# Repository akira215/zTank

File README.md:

# zTank
Tank survey, embedded sofware on dedicated PCB using ESP32C6 µC

# Description

This repository contain all the development for an electronic device that will monitor a water tank (such as rain collect tank) using zigbee to transmit data to a coordinator. It contains: 
 * A PCB design [PCB design](PCB/README.md)
 * An enclosure design to be printed in 3D [Enclosure design](3Dprint/README.md)
 * Source code of the embedded software on the board (in an ESP32C6 µC)
 * An External converter for Zigbee2MQTT service [external converter](external_converters)

# Principle

The board will collect data from various sensors surch as:
 * Upstream static pressure (pump side)
 * Downstream static pressure (home side) - difference between upstream and downstream static pressure is used to estimate filters clogging
 * Water level sensor, to estimate the available water volume in the tank
 * water pulse meter to count the consumption in the home
 * Additionally on board temperature sensor could be monitor

 The 3 first sensors shall be 4-20mA sensor directly connected to the board. The water counter shall be a dry contact meter, connected to the board

 All these sensors have a calibration factor that can be updated directly form Zigbee2MQTT GUI. To avoid losing calibration, the device itself will keep updated theses factor in its Non Volatile Storage.

A 4-20mA input is available for any other futher sensor requirement. Adding a sensor will require to :
 * Update the embedded software
 * Update the external converter on Zigbee2MQTT side

## Usage

  * Short press button to join the zigbee network (coordinator shall grant pairing) -> LED shall flash, until network is joined, it then shutoff
  * Long press button to leave network. When the LED is fixed on, the device is not connected to the network neither is trying to join

## Sensor selection

### Upstream and downstream static pressure

  Regular pressure transmitter are not so expensive and efficient for that purpose. These 2 sensors shall have a measured range according to installation pressure. In regular network, pressure is limited to 3 bars, so selecting a sensor 0-5 bars seems a good choice. If the upper value is higher, the resolution of the measurement will be less as the ADC converter resolution is fixed.

  The shunt to convert current to tension for the ADC converter is 133R, and Imax for the sensor @max range will be 20mA so Umax for ADS1115 will be 2.66V (U=R*I). 5 bars = 500 kPa, so the calibration factor shall be 500 kPa / 2.66V = 187.97 kPa/V. Of course this factor shall be adjusted by measuring at the same location of one sensor the pressure, and correcting the reading of the sensor, but this short computation can help to start setting up calibration factor

### Water level

  Whatever technology of sensor could be used as soon as its output is 4-20mA current. Tests have been done using submerged differential pressure sensor, with the balance pipe to get the atmospheric pressure that run with the electrical cable, they worked properly. The range of this sensor shall be in accordance with the depth of the tank. The output value of Zigbee2MQTT will be a % of depth (meaning 100% when tank is full). Depending on the shape and cross section of the tank, this could be converted to a volume directly in the Z2M external converter, or outside Z2M in another software.

  The shunt to convert current to tension for the ADC converter is 133R, and Imax for the sensor @max range will be 20mA so Umax for ADS1115 will be 2.66V (U=R*I). For 100% the calibration factor shall be 100% / 2.66V = 37.594 %/V. 
  
  Of course this factor shall be adjusted when tank is full to read 100% in the Zigbee2MQTT output. For example, if yo have a 0-2m sensor and the require stroke of your tank (max height - min height before depriming pump) is 1.5m, it means that the 100% value of your tank will occur when sensor will read 1.5m (take care to install the sensor just before depriming pump). The voltage at the converter will be 1.5m/2m * 2.66V = 1.995V, so you will have to set the calibration factor considering 100% / 1.995V = 50.125%/V

### Water pulse counter

  The water meter shall send a pulse each XX L, whatever XX is. It is expected to have a dry contact that switch on and off each pulse. Hardware debouncer has been implemented for a particular counter, measuring bouncing using an oscilloscope. Computation of this RC filter has been provided here:
  [Spreadsheet](<PCB/2024-06-29 Comput.ods>)
    
  The kFactor to be set up in Zigbee2MQTT is only the L per pulse of the counter.

## Zigbee2MQTT integration

### External converter

External converter shall be loaded according to Zigbee2MQTT instructions:

[Zigbee2MQTT external converters](https://www.zigbee2mqtt.io/advanced/more/external_converters.html)

Restart Zigbee2MQTT `Webpage > Settings > Tools > Restart Zigbee2MQTT`

### Pairing zTank device

If the LED is fixed on, short press one time on the button, this will put the device in pairing mode.
Device is in Pairing Mode when the LED flahes quickly. 

Put Coordinator (or other device) in pairing mode using Zigbee2MQTT GUI (antenna symbol on the upper right of the screen with mention `All`)

After a short time, LED shall stop flashing. When LED is off, device is paired. You can check on Zigbee2MQTT device list

### Device icon

To add an icon in Zigbee2MQTT GUI, create a folder named `device_icon` in the root of Zigbee2MQTT docker installation (folder containing `configuration.yml`). In that foler, put the `zTank_icon.png` file contained in the `img` directory of this repository.

On Zigbee2MQTT GUI, go to `Devices` list and click on the device. Go to `Settings` tab and scroll down to the `icon` box.
Put `device_icons/zTank_icon.png` in that box. Icon shall be visible on Zigbee2MQTT GUI.

### Reporting

To develop*******************************************************************

## Build Instructions

The embedded software required `esp-ash-components`:

```
git submodule add https://github.com/akira215/esp-ash-components.git components
```

Create a partition.csv for zigbee and configure menuconfig with custom partition table (shall be done by default)

## Configuration

Configuration is available in `menuconfig` in the `Project setting` section:

### Pin Layout

  This section refer to hardware connection of LED button and volume meter. <span style="color:red">**These settings shall not be changed unless new hardware is developped.**</span>

### Zigbee endpoints

  This section refer to the endpoint for each sensor of the device. Any change in this number require to update the external converter accordingly

  And in Zigbee2MQTT external converter:

### Zigbee device

  Zigbee stack has been sized doing extensive tests. <span style="color:red">**This setting shall not be changed.**</span>

### ADS Pin Layout

  This section refer to hardware connection of ADS1115 converter to µC pin. <span style="color:red">**These settings shall not be changed unless new hardware is developped.**</span>

### ADS Converter config

  The first 3 inputs refer to the channel in which each sensor is connected. Take care that channel are not implemented on the connector in a logical order, so please refer to pictures that describe which pins of the connector is connected to which ADC channel (and polarity for sensors)

  The delay between 2 queries of ADS is the update rate of the measurement. Between 2 measurement, ADS is put in sleep to optimize consumption. Take care that driver will trigger one conversion for each channel, so there is a minimal time between 2 queries, depending on the resolution set for the ADS.

  The delay between 2 queries of temperature is the update rate of the measurement of the internal µC temperature sensor.

## Current Status

Still work in progress, but is completely running. All bugs 
could be reported to try to improve it.

## PCB design

[PCB design](PCB/README.md)

## Enclosure design design

[Enclosure design](3Dprint/README.md)

## Caveats

### To be developped

OTA update

## Usage and Examples

## Changes

### New in version 0.0.0

## Credits

 * [Zigbee2MQTT](https://github.com/Koenkk/zigbee2mqtt)

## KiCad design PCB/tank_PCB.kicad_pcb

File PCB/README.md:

# zTank PCB
A dedicated PCB using ESP32C6 µC as been designed to optimize reliability and costs.

## Tools

 The design of the PCB has been done with KiCad 9.0. Particular footprint and 3D STEP file are included in the `/footprints` folder for sake of maintenance

## Design

 The design is based on ESP32C6 WROOM with the following peripherials:
 - USB for power, flash device and output serial debug / info.
 - Powering circuit is done using MCP1826S 
 - A 4-20mA loop is built based on a LM2735X (1.6MHz) to raise voltage to about 20V
 - 4 channels 4-20mA sensors is provided and converted using ADS1115IDGS. It communicate with µC with i2c port
 - a debounced contact is provided for pulse counter
 - A push button is also provided for very simple HMI
 - PCB is also equipped by a LED for simpl HMI
 - Finally PCB is equipped with header that can be used for a touchscreen device in case of future needs (software lib already written and tested)

 Component size has been selected to 0805, except ESD protective diodes that are smaller.

### USB

  USB socket is grounded to the main ground planes (2 sides).
  USB Lines `USB-` and `USB+` are directly connected to ESP32C6 to flash and monitor µC.
  `VBUS` is used to provide `+5V` (which is in fact lower than +5V) via a protective diode `D3`.

  All this 3 lines are protected by ESD protective diode.

### Voltage regulator

  All the board is powered using `+3.3V`. This voltage is provided by a fixed low-voltage regulator MCP1826S-3302E that can provide up to 1000mA.
  Fixed voltage regulator requires only few external component, in this case only capacitors are installed as per datasheet.

### 4-20mA Voltage circuit

  To avoid noise on lines and due to voltage drop at each stage, 4-20mA loop voltage shall be at around 20V. Care shall be taken when changing this voltage as it may require adjustment (in the shunt values for instance) to avoid damaging other components.

  This voltage is produced from `+5V` using a boost type regulator LM2735X (@1.6MHz). Computation of the external components are provided in the LibreOffice Spreadsheet [PCB comput spreadsheet](<2024-06-29 Comput.ods>). A 33µH inductance has been selected to get a clean output voltage to avoid noise on sensors line.

### 4-20mA conversion

  4 channels are available via Phoenix contact 8 poles connector. Each channel input current is injected in a 133R shunt (low tolerance resistor) to output a voltage below 3.3V. A 100nF capacitor is provided to reduce noise.

  Each channel voltage is then converted in a digital signal using an ADS1115IDGS, that communicate with µC using i2c protocol. A ready pin is used to trigger an interrupt to the µC when data are available.
  External components are:
   - 10k resistor connected to the ground for the address of the device (only one on board so gnd is the common one)
   - 10k pull-up resistor on each signal (`SCL`, `SDA`, `RDY`) connected to µC
   - decoupling capacitor for power lines and rearmable fuse to protect circuit

### Debounced contact

### µC ESP32C6 WROOM

### Push Button

### Led

### Header

## PCB fabrication

## Assembly

## Usage

### To be developped

## Credits

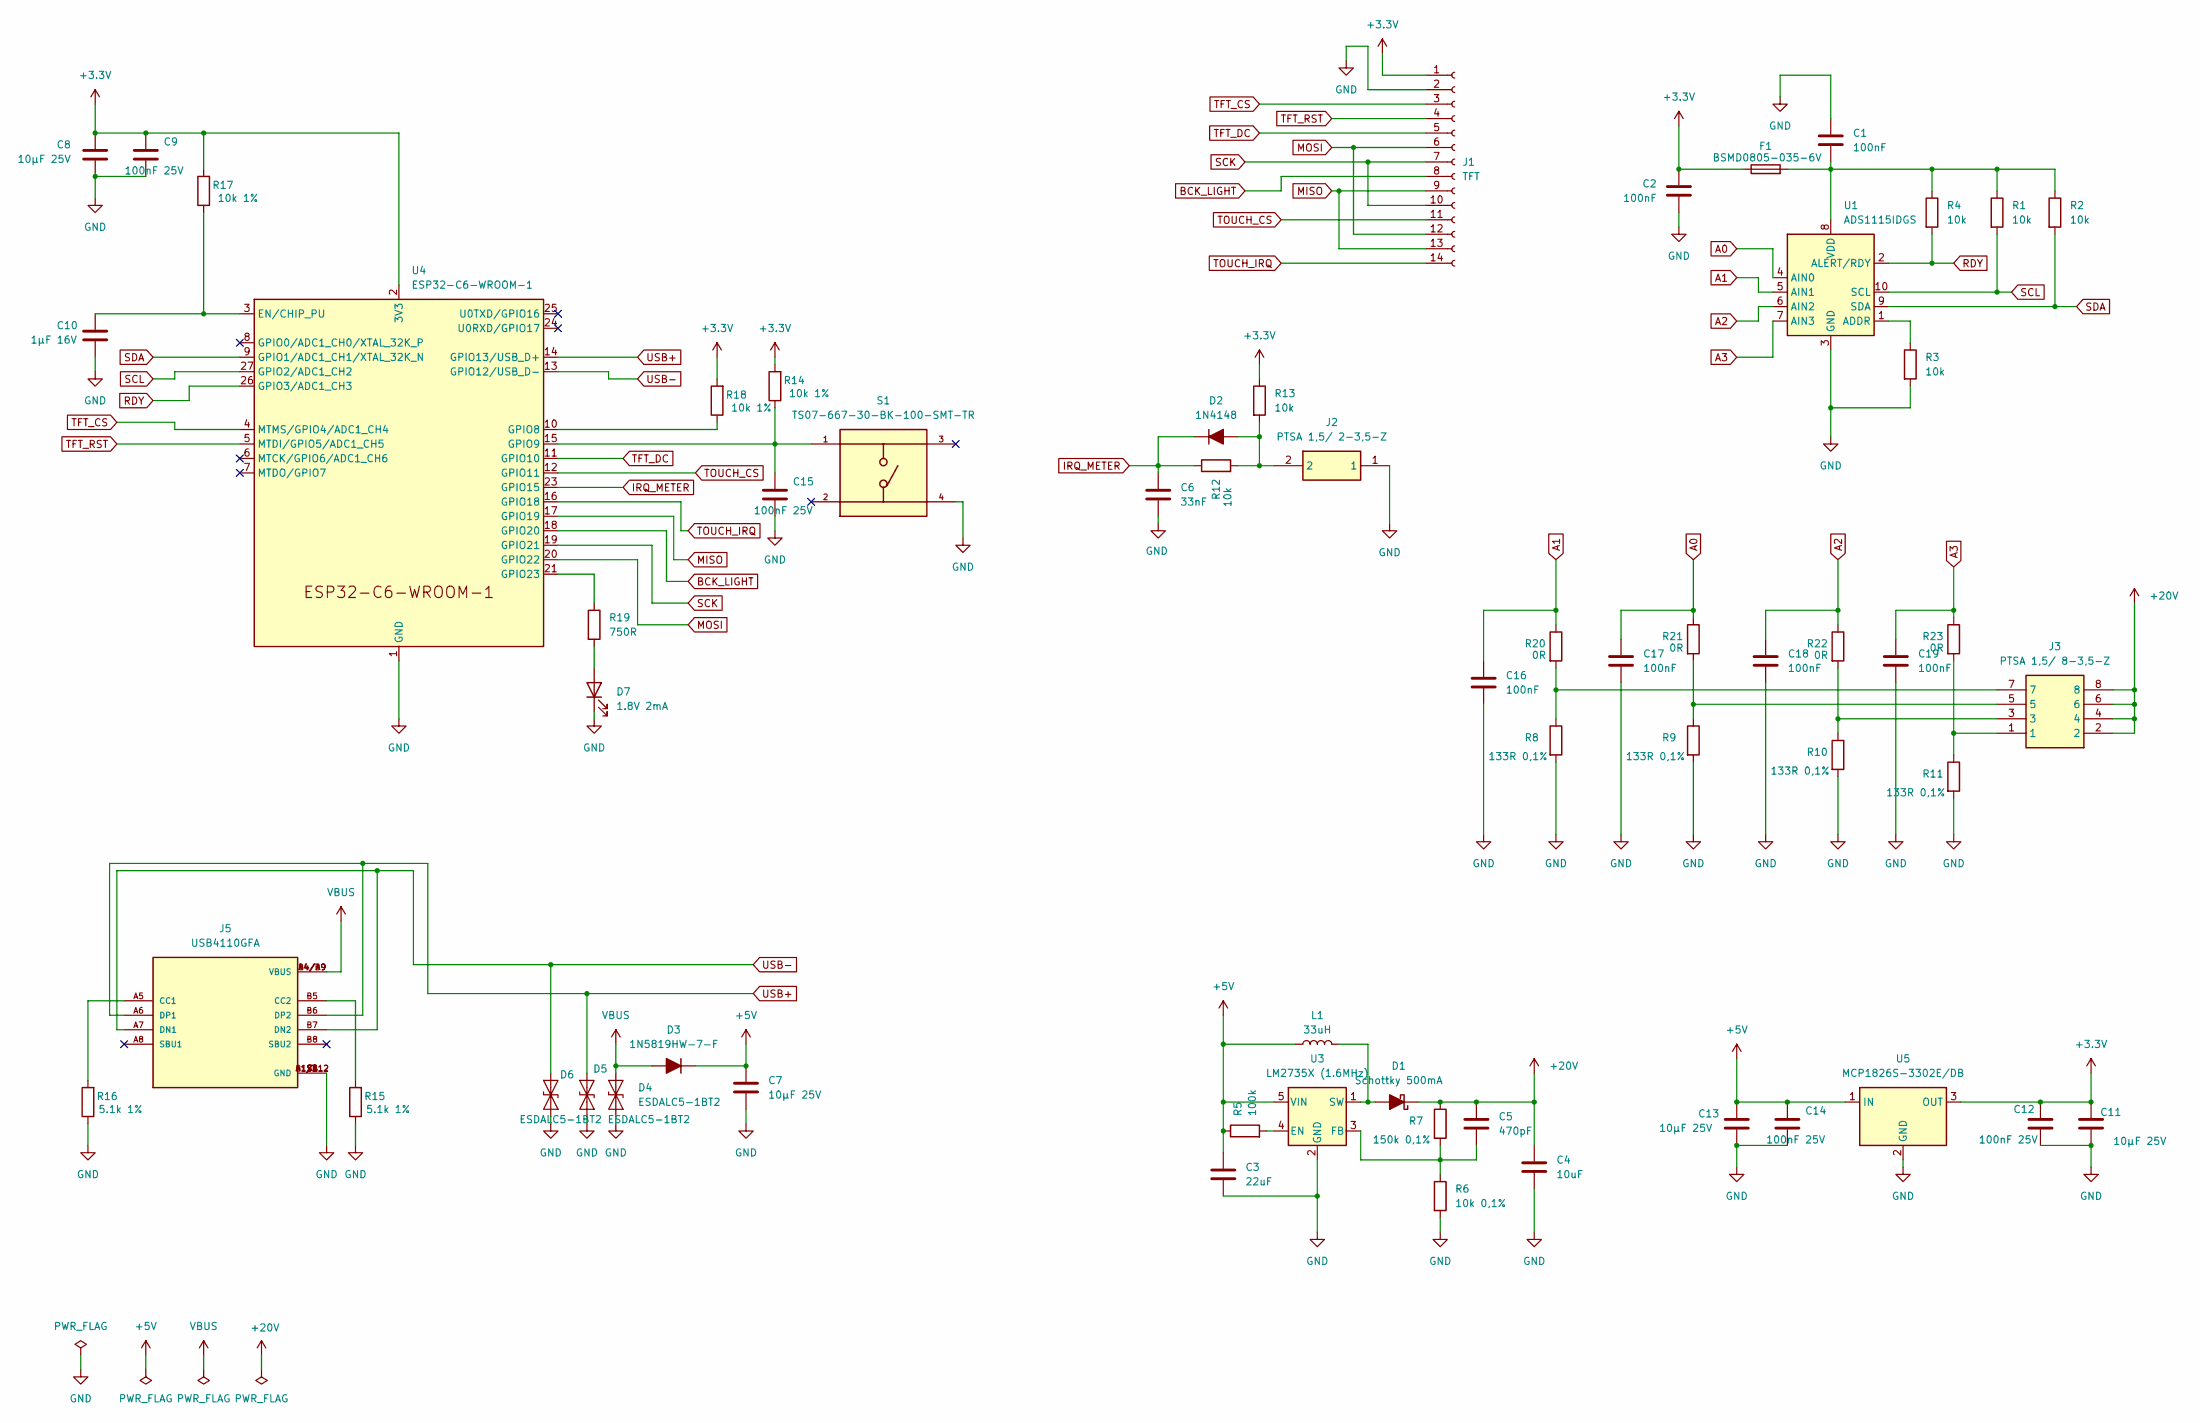
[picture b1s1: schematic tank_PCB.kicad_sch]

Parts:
C1, C2, C16, C17, C18, C19: 100nF; C_0805_2012Metric_Pad1.18x1.45mm_HandSolder
C3: 22uF; C_0805_2012Metric_Pad1.18x1.45mm_HandSolder
C4: 10uF; C_0805_2012Metric_Pad1.18x1.45mm_HandSolder
C5: 470pF; C_0805_2012Metric_Pad1.18x1.45mm_HandSolder
C6: 33nF; C_0805_2012Metric_Pad1.18x1.45mm_HandSolder
C7, C8, C11, C13: 10µF 25V; C_0805_2012Metric_Pad1.18x1.45mm_HandSolder
C9, C12, C14, C15: 100nF 25V; C_0805_2012Metric_Pad1.18x1.45mm_HandSolder
C10: 1µF 16V; C_0805_2012Metric_Pad1.18x1.45mm_HandSolder
D1: Schottky 500mA; D_SOD-123
D2: 1N4148; D_SOD-323_HandSoldering
D3: 1N5819HW-7-F; D_SOD-123
D4, D5, D6: ESDALC5-1BT2; D_SOD-882D
D7: 1.8V 2mA; D_0805_2012Metric_Pad1.15x1.40mm_HandSolder
F1: BSMD0805-035-6V; Fuse_0805_2012Metric
J1: TFT; PinHeader_1x14_P2.54mm_Vertical
J2: PTSA 1,5/ 2-3,5-Z; Phoenix Contact PTSA 2; Manufacturer_Part_Number 1985195; Mouser Part Number 651-1985195
J3: PTSA 1,5/ 8-3,5-Z; Phoenix Contact PTSA 8; Manufacturer_Part_Number 1985250; Mouser Part Number 651-1985250
J5: USB4110GFA; GCT_USB4110GFA
L1: 33uH; L_10.4x10.4_H4.8
R1, R2, R3, R4, R12, R13: 10k; R_0805_2012Metric_Pad1.20x1.40mm_HandSolder
R5: 100k; R_0805_2012Metric_Pad1.20x1.40mm_HandSolder
R6: 10k 0,1%; R_0805_2012Metric_Pad1.20x1.40mm_HandSolder
R7: 150k 0,1%; R_0805_2012Metric_Pad1.20x1.40mm_HandSolder
R8, R9, R10, R11: 133R 0,1%; R_0805_2012Metric_Pad1.20x1.40mm_HandSolder
R14, R17, R18: 10k 1%; R_0805_2012Metric_Pad1.20x1.40mm_HandSolder
R15, R16: 5.1k 1%; R_0805_2012Metric_Pad1.20x1.40mm_HandSolder
R19: 750R; R_0805_2012Metric_Pad1.20x1.40mm_HandSolder
R20, R21, R22, R23: 0R; R_0805_2012Metric_Pad1.20x1.40mm_HandSolder
S1: TS07-667-30-BK-100-SMT-TR; CUI switch SW_TS07-667-30-BK-100-SMT-TR; PARTREV 1.0
U1: ADS1115IDGS; TSSOP-10_3x3mm_P0.5mm
U3: LM2735X (1.6MHz); SOT-23-5
U4: ESP32-C6-WROOM-1
U5: MCP1826S-3302E/DB; SOT-223-3_TabPin2

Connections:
+3.3V: C2.1, C8.1, C9.1, C11.1, C12.1, F1.1, J1.1, R13.1, R14.2, R17.2, R18.2, U4.2 (3V3), U5.3 (OUT)
+5V: C3.1, C7.1, C13.1, C14.1, D3.1 (K), L1.1, R5.1, U3.5 (VIN), U5.1 (IN)
+20V: C4.1, C5.1, D1.1 (K), J3.2, J3.4, J3.6, J3.8, R7.1
A0: C17.1, R21.1, U1.4 (AIN0)
A1: C16.1, R20.1, U1.5 (AIN1)
A2: C18.1, R22.1, U1.6 (AIN2)
A3: C19.1, R23.1, U1.7 (AIN3)
BCK_LIGHT: J1.8, U4.18 (GPIO20)
GND: C1.1, C2.2, C3.2, C4.2, C6.2, C7.2, C8.2, C9.2, C10.2, C11.2, C12.2, C13.2, C14.2, C15.2, C16.2, C17.2, C18.2, C19.2, D4.1 (A1), D5.1 (A1), D6.1 (A1), D7.1 (K), J1.2, J2.1, J5.A1/B12 (GND), J5.B1/A12 (GND), J5.S1 (GND), J5.S2 (GND), J5.S3 (GND), J5.S4 (GND), R3.2, R6.2, R8.2, R9.2, R10.2, R11.2, R15.1, R16.1, S1.4, U1.3 (GND), U3.2 (GND), U4.1 (GND), U4.28 (GND), U4.29 (GND), U5.2 (GND)
IRQ_METER: C6.1, D2.1 (K), R12.1, U4.23 (GPIO15)
MISO: J1.9, J1.13, U4.17 (GPIO19)
MOSI: J1.6, J1.12, U4.20 (GPIO22)
unnamed: D1.2 (A), L1.2, U3.1 (SW)
unnamed: D2.2 (A), J2.2, R12.2, R13.2
unnamed: D7.2 (A), R19.2
unnamed: J3.1, R11.1, R23.2
unnamed: J3.3, R10.1, R22.2
unnamed: J3.5, R9.1, R21.2
unnamed: J3.7, R8.1, R20.2
unnamed: J5.A5 (CC1), R16.2
unnamed: J5.B5 (CC2), R15.2
unnamed: R3.1, U1.1 (ADDR)
unnamed: C1.2, F1.2, R1.1, R2.1, R4.1, U1.8 (VDD)
unnamed: R5.2, U3.4 (EN)
unnamed: C5.2, R6.1, R7.2, U3.3 (FB)
unnamed: C10.1, R17.1, U4.3 (EN/CHIP_PU)
unnamed: R18.1, U4.10 (GPIO8)
unnamed: C15.1, R14.1, S1.1, U4.15 (GPIO9)
unnamed: R19.1, U4.21 (GPIO23)
RDY: R4.2, U1.2 (ALERT/RDY), U4.26 (GPIO3/ADC1_CH3)
SCK: J1.7, J1.10, U4.19 (GPIO21)
SCL: R1.2, U1.10 (SCL), U4.27 (GPIO2/ADC1_CH2)
SDA: R2.2, U1.9 (SDA), U4.9 (GPIO1/ADC1_CH1/XTAL_32K_N)
TFT_CS: J1.3, U4.4 (MTMS/GPIO4/ADC1_CH4)
TFT_DC: J1.5, U4.11 (GPIO10)
TFT_RST: J1.4, U4.5 (MTDI/GPIO5/ADC1_CH5)
TOUCH_CS: J1.11, U4.12 (GPIO11)
TOUCH_IRQ: J1.14, U4.16 (GPIO18)
USB+: D5.2 (A2), J5.A6 (DP1), J5.B6 (DP2), U4.14 (GPIO13/USB_D+)
USB-: D6.2 (A2), J5.A7 (DN1), J5.B7 (DN2), U4.13 (GPIO12/USB_D-)
VBUS: D3.2 (A), D4.2 (A2), J5.A4/B9 (VBUS), J5.B4/A9 (VBUS)

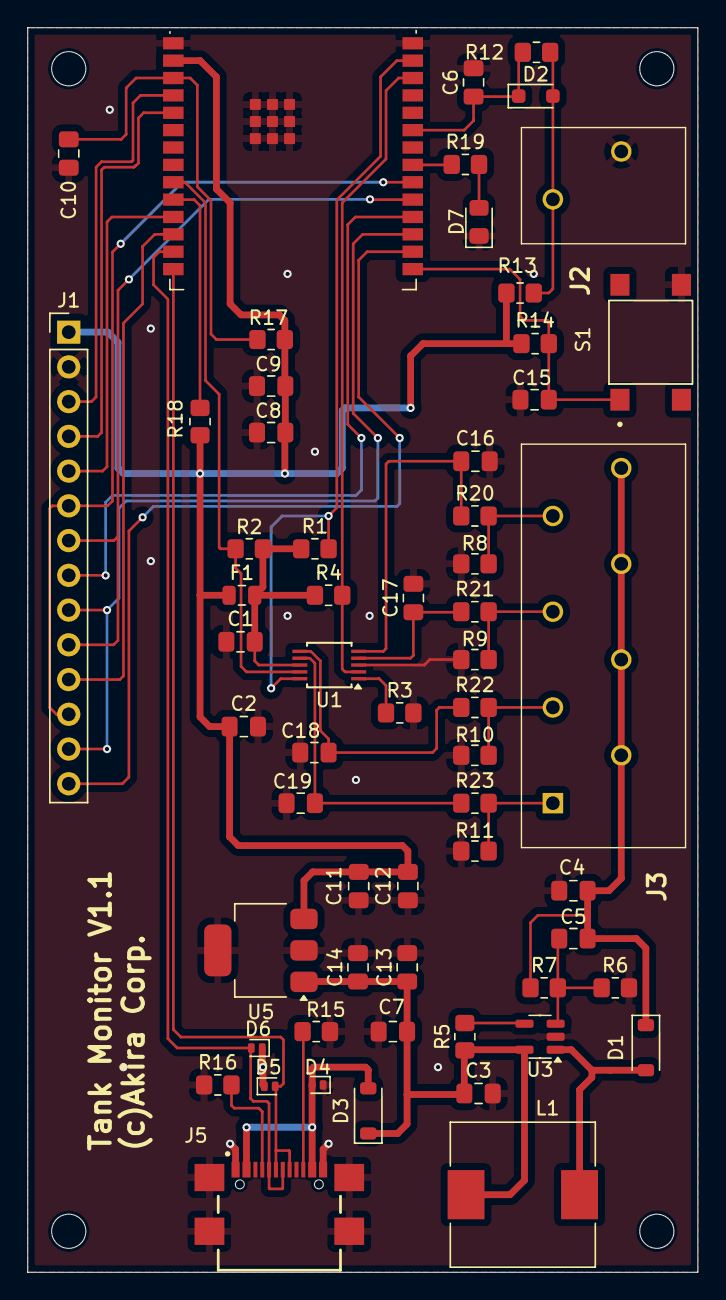
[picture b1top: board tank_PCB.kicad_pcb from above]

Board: 2 copper layers, 49.0 x 91.0 mm, 60 parts (0 on the bottom side), 41 nets.

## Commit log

2024-09-23 working stack
2024-09-30 volumetric meter on going
2024-10-01 testing flowmeter
2024-10-02 increasing event loop stack (double)
2024-10-02 testing event
2024-10-07 Testing event loop
2024-10-08 readint time
2024-10-11 ok with zbnode event
2024-10-21 adding PCB
2024-10-21 updating component
2024-10-21 removing PCB bckup tracking
2024-10-21 adding screenshot
2024-11-15 Multiplier from HA working
2024-11-22 reporting watermeter
2024-11-26 Testing custom attribute
2024-11-27 testing custom attribute Ok
2025-08-01 updating components versions
2025-08-20 Work on WaterFLow
2025-08-21 updating PCB Kicad v9
2025-08-21 Correcting PCB bug J3 pin 7 at GND
2025-08-21 Creating sdkconfig.defaults and putting sdkconfig to gitignore
2025-08-21 updating gitignore
2025-08-21 untrack files
2025-08-22 WIP on adsDriver
2025-08-22 WIP adsdriver callback errors + NVS value error
2025-08-24 AdsDriver callback working
2025-08-24 WaterPressureMeas working
2025-08-24 Correction default pFactor
2025-08-25 Pressure Cluster error handle writing persistent value
2025-08-30 Uptating WaterPressureMeas
2025-08-31 issuing JLPCB gerber files
2025-08-31 Correcting log WaterFlowMeasCluster
2025-08-31 All cluster implemented
2025-09-01 Working on enclosure
2025-09-01 deleting gitignore in PCB folder
2025-09-11 Finalizing enclosure design and Readme
2025-09-11 WIP on readme PCB
2025-09-15 Working on documentation
2025-09-16 WIP readme
2025-09-17 WIP on doc
2025-09-27 waterflow daily reset
2025-09-27 Correcting waterflow cluster
2025-09-27 Adding LICENSE
2025-10-04 Clearing Kicad Warnings
2025-10-20 default setting to Zigbee router
2025-10-25 remove ununsed method
